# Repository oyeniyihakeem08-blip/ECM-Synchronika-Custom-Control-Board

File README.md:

Project Description

This specification defines a custom control PCB to replace the factory GICAR control board and PID controller in an ECM Synchronika dual-boiler espresso machine. The design must be:

- **Plug & Play**: Direct replacement using existing machine wiring
- **Reversible**: Original equipment can be reinstalled without modification
- **Universal Voltage**: Support 100-240V AC, 50/60Hz worldwide operation
- **Production Ready**: Suitable for small-batch or volume manufacturing

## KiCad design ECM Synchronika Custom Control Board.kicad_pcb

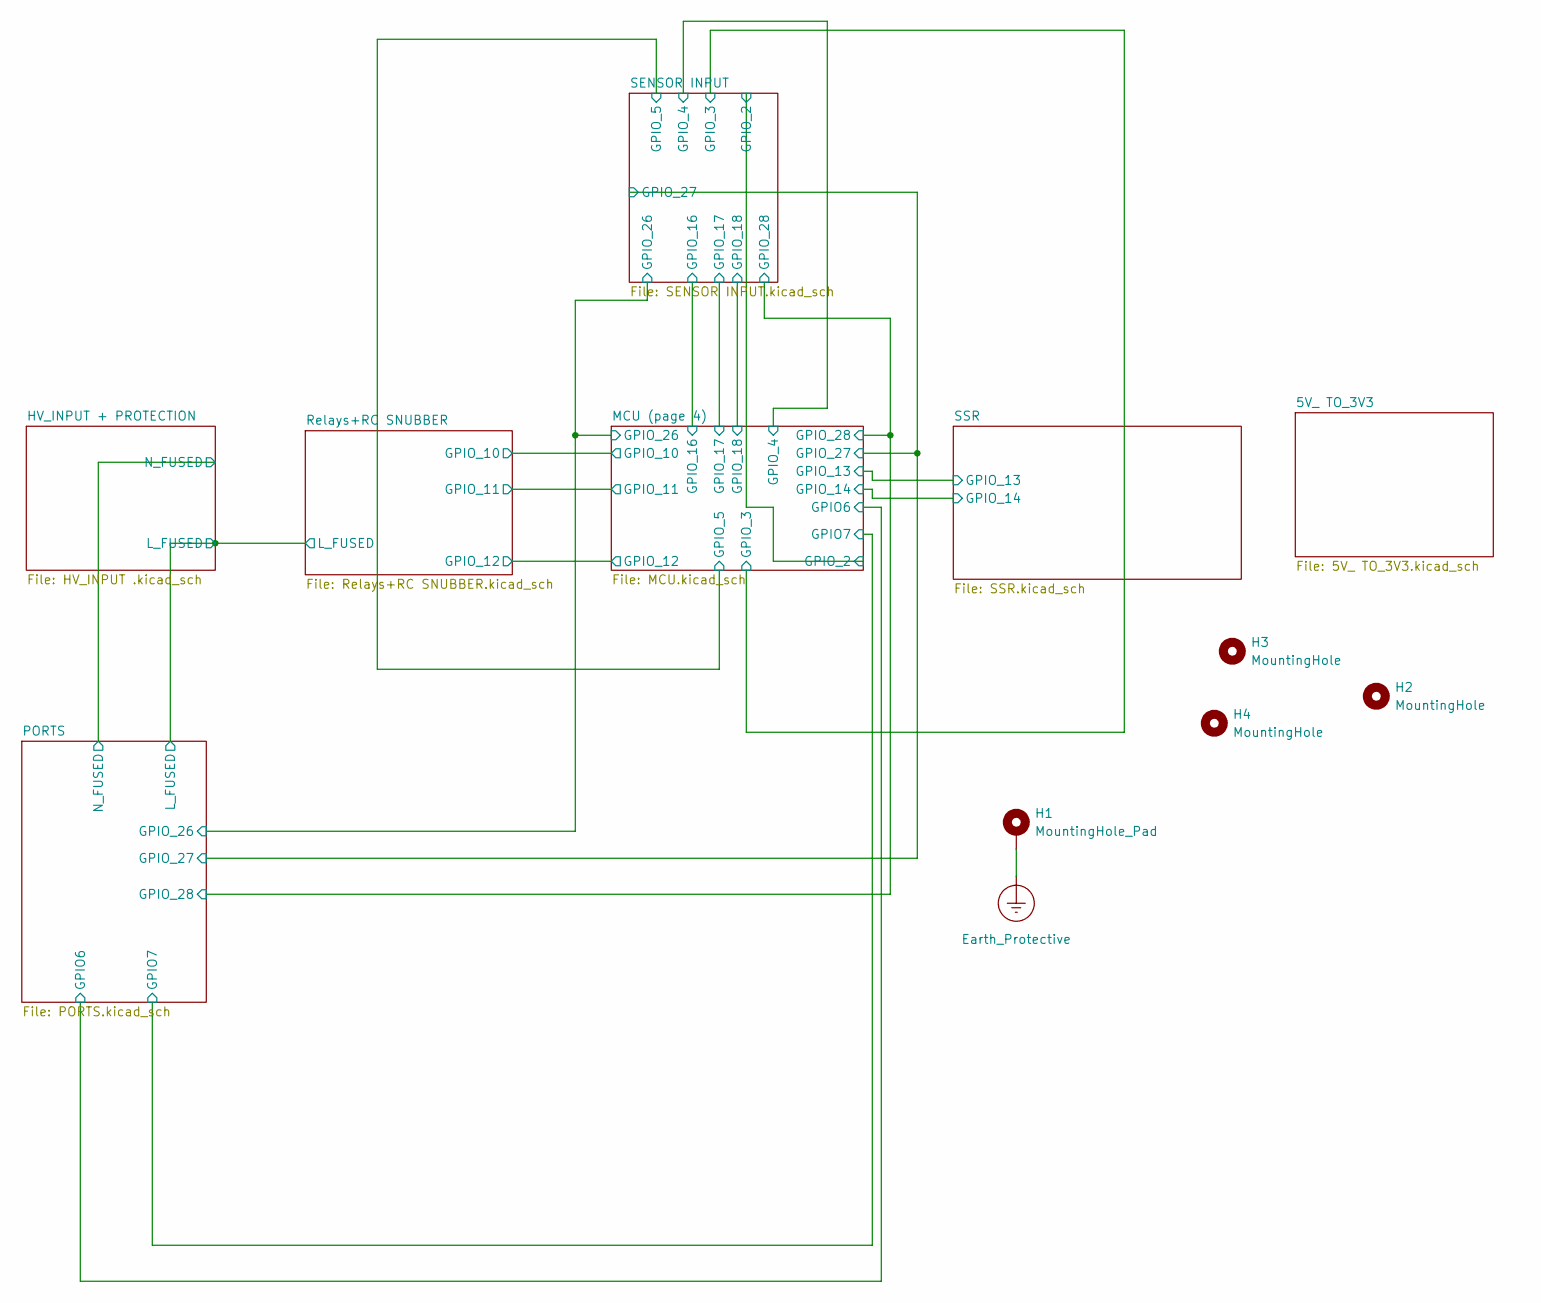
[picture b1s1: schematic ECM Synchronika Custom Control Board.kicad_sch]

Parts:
H1: MountingHole_Pad; MountingHole_3.2mm_M3_ISO7380_Pad_TopBottom
H2, H3, H4: MountingHole; MountingHole_3.2mm_M3_ISO14580

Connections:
Earth_Protective: H1.1; also elsewhere on the board

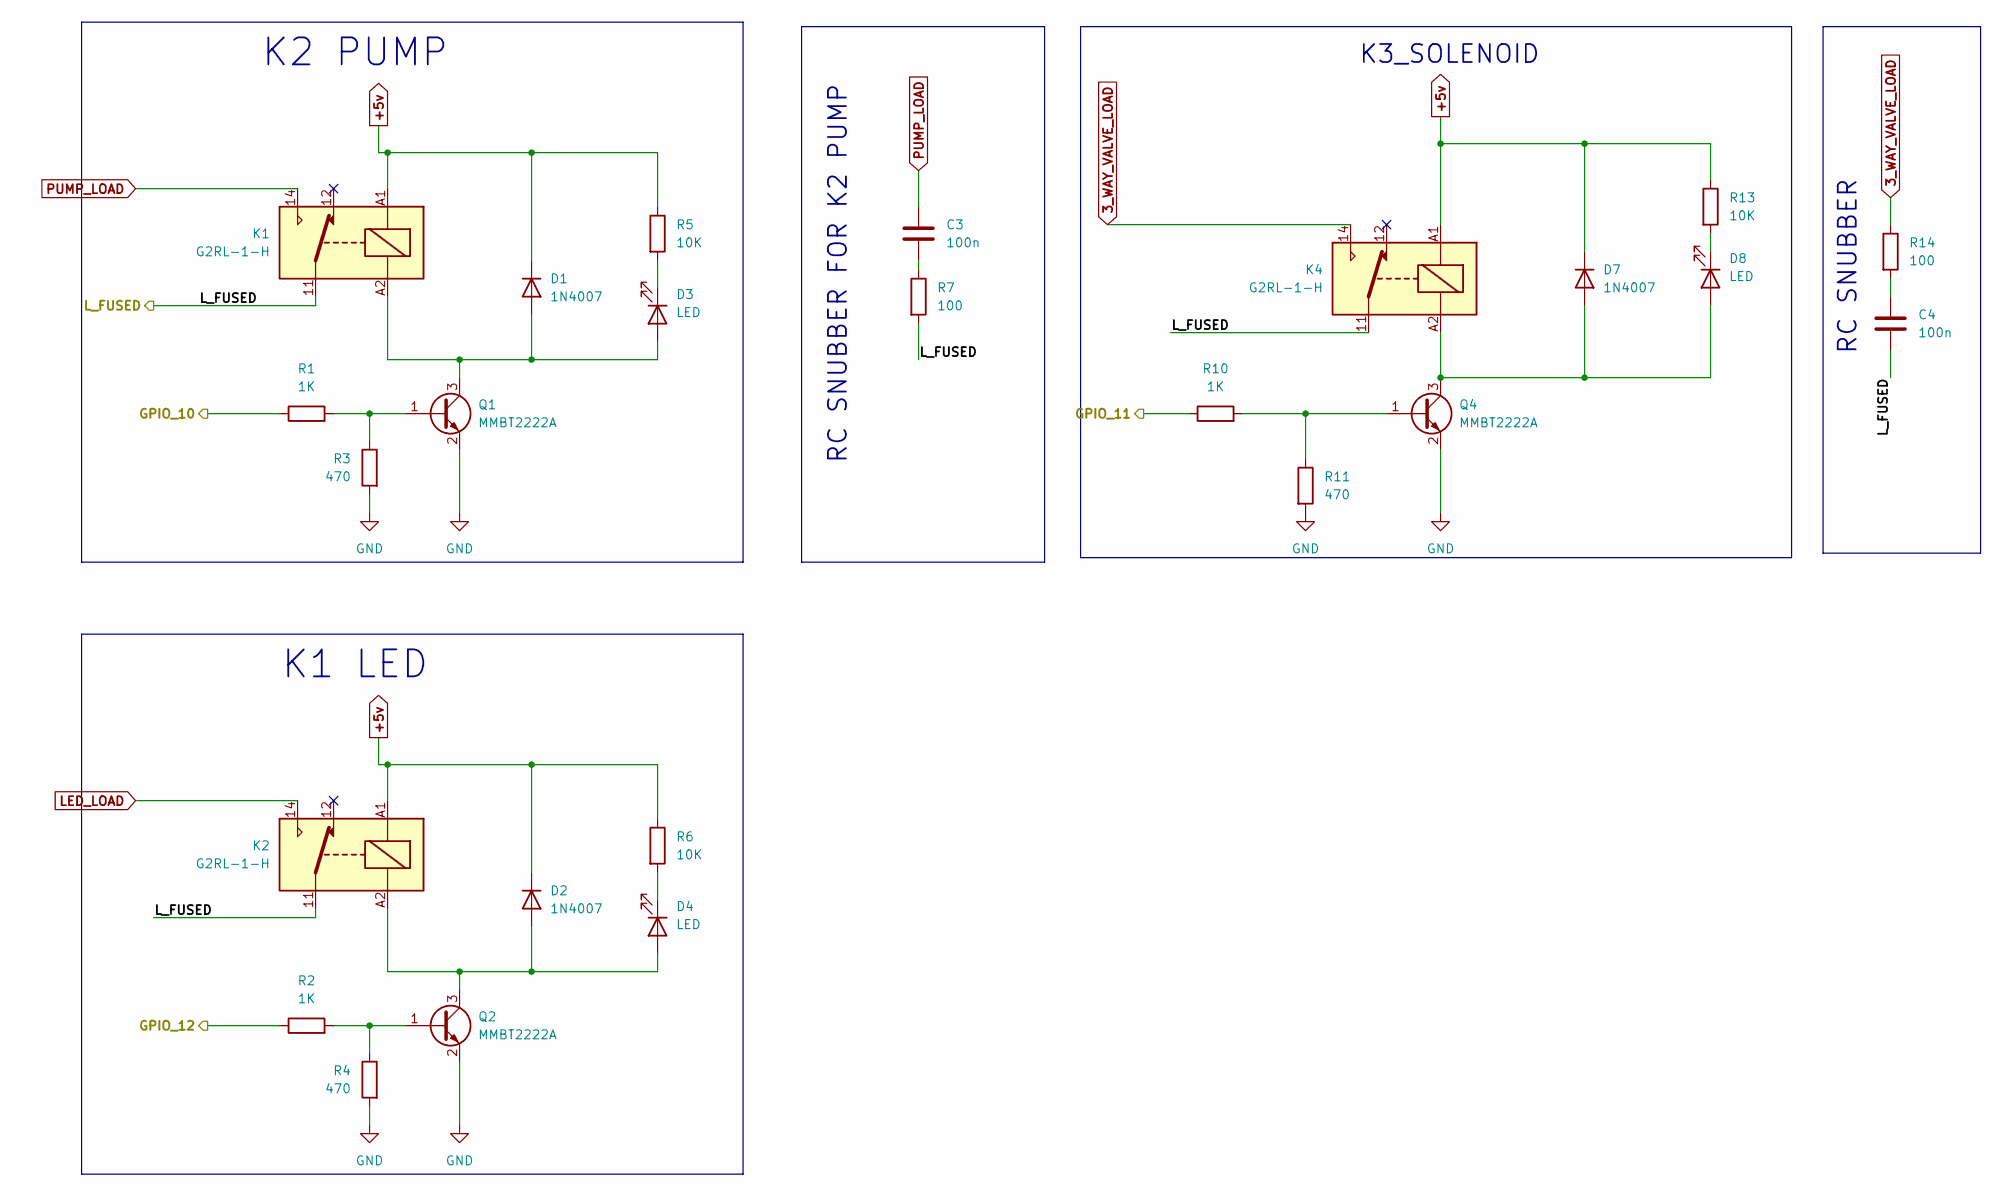
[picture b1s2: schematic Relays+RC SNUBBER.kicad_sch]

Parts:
C3, C4: 100n; C_Rect_L26.5mm_W11.5mm_P22.50mm_MKS4
D1, D2, D7: 1N4007; D_SMA
D3, D4, D8: LED; LED_0805_2012Metric
K1, K2, K4: G2RL-1-H; Relay_SPDT_Omron_G2RL-1 MODIFIED
Q1, Q2, Q4: MMBT2222A; SOT-23
R1, R2, R10: 1K; R_0805_2012Metric
R3, R4, R11: 470; R_0805_2012Metric
R5, R6, R13: 10K; R_0805_2012Metric
R7, R14: 100; R_1210_3225Metric

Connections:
3_WAY_VALVE_LOAD: K4.14, R14.1; also elsewhere on the board
+5v: D1.1 (K), D2.1 (K), D7.1 (K), K1.A1, K2.A1, K4.A1, R5.1, R6.1, R13.1; also elsewhere on the board
/HV_INPUT + PROTECTION/L_FUSED: C4.2, K1.11, K2.11, K4.11, R7.2; also elsewhere on the board
/MCU (page 4)/GPIO_10: R1.1; also elsewhere on the board
/MCU (page 4)/GPIO_11: R10.1; also elsewhere on the board
/MCU (page 4)/GPIO_12: R2.1; also elsewhere on the board
GND: Q1.2 (E), Q2.2 (E), Q4.2 (E), R3.2, R4.2, R11.2; also elsewhere on the board
LED_LOAD: K2.14; also elsewhere on the board
unnamed: C3.2, R7.1
unnamed: C4.1, R14.2
unnamed: D1.2 (A), D3.2 (A), K1.A2, Q1.3 (C)
unnamed: D2.2 (A), D4.2 (A), K2.A2, Q2.3 (C)
unnamed: D3.1 (K), R5.2
unnamed: D4.1 (K), R6.2
unnamed: D7.2 (A), D8.2 (A), K4.A2, Q4.3 (C)
unnamed: D8.1 (K), R13.2
unnamed: Q1.1 (B), R1.2, R3.1
unnamed: Q2.1 (B), R2.2, R4.1
unnamed: Q4.1 (B), R10.2, R11.1
PUMP_LOAD: C3.1, K1.14; also elsewhere on the board

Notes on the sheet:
K1 LED
RC SNUBBER
K2 PUMP
RC SNUBBER FOR K2 PUMP
K3_SOLENOID

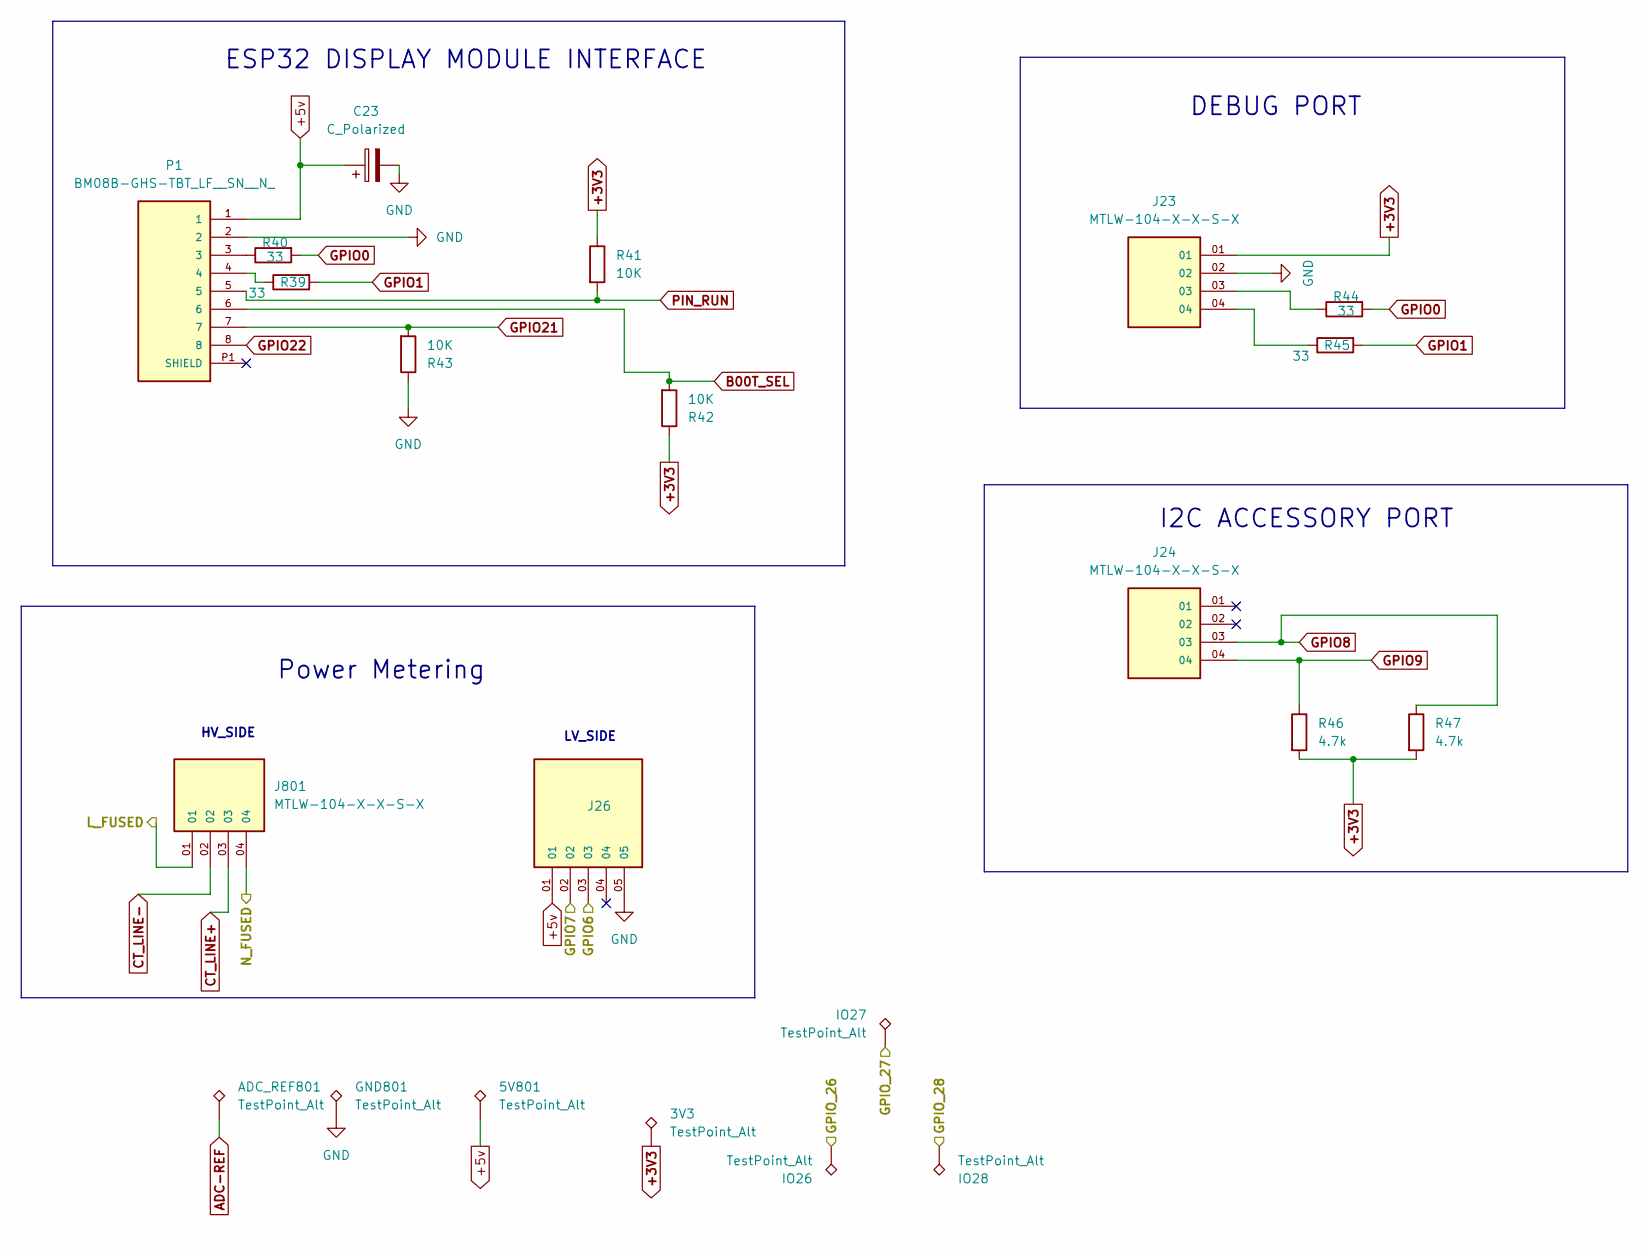
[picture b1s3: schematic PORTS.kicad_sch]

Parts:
3V3, 5V801: TestPoint_Alt; Pin_D1.0mm_L10.0mm_LooseFit
ADC_REF801: TestPoint_Alt; Pin_D1.0mm_L10.0mm_LooseFit
C23: C_Polarized; CP_Elec_5x5.4
GND801: TestPoint_Alt; Pin_D1.0mm_L10.0mm_LooseFit
IO26, IO27, IO28: TestPoint_Alt; Pin_D1.0mm_L10.0mm_LooseFit
J23, J24, J801: MTLW-104-X-X-S-X; SAMTEC_MTLW-104-X-X-S-X; PARTREV A
J26: TSW-105-05-L-S-LL; SAMTEC_TSW-105-05-L-S-LL; PARTREV R
P1: BM08B-GHS-TBT_LF__SN__N_; JST_BM08B-GHS-TBT_LF__SN__N_
R39, R40, R44, R45: 33; R_0805_2012Metric
R41, R42, R43: 10K; R_0603_1608Metric
R46, R47: 4.7k; R_0603_1608Metric

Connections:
+3V3: 3V3.1, J23.01, R41.1, R42.1, R46.2, R47.2; also elsewhere on the board
+5v: 5V801.1, C23.1, J26.01, P1.1; also elsewhere on the board
/HV_INPUT + PROTECTION/L_FUSED: J801.01; also elsewhere on the board
/HV_INPUT + PROTECTION/N_FUSED: J801.04; also elsewhere on the board
/MCU (page 4)/GPIO6: J26.03; also elsewhere on the board
/MCU (page 4)/GPIO7: J26.02; also elsewhere on the board
/MCU (page 4)/GPIO_26: IO26.1; also elsewhere on the board
/MCU (page 4)/GPIO_27: IO27.1; also elsewhere on the board
/SENSOR INPUT/GPIO_28: IO28.1; also elsewhere on the board
ADC-REF: ADC_REF801.1; also elsewhere on the board
B00T_SEL: P1.6, R42.2; also elsewhere on the board
CT_LINE+: J801.03; also elsewhere on the board
CT_LINE-: J801.02; also elsewhere on the board
GND: C23.2, GND801.1, J23.02, J26.05, P1.2, R43.1; also elsewhere on the board
GPIO0: R40.2, R44.2; also elsewhere on the board
GPIO1: R39.2, R45.2; also elsewhere on the board
GPIO8: J24.03, R47.1; also elsewhere on the board
GPIO9: J24.04, R46.1; also elsewhere on the board
GPIO21: P1.7, R43.2; also elsewhere on the board
GPIO22: P1.8; also elsewhere on the board
unnamed: J23.03, R44.1
unnamed: J23.04, R45.1
unnamed: P1.3, R40.1
unnamed: P1.4, R39.1
PIN_RUN: P1.5, R41.2; also elsewhere on the board

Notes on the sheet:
DEBUG PORT
ESP32 DISPLAY MODULE INTERFACE
I2C ACCESSORY PORT
HV_SIDE
LV_SIDE
Power Metering

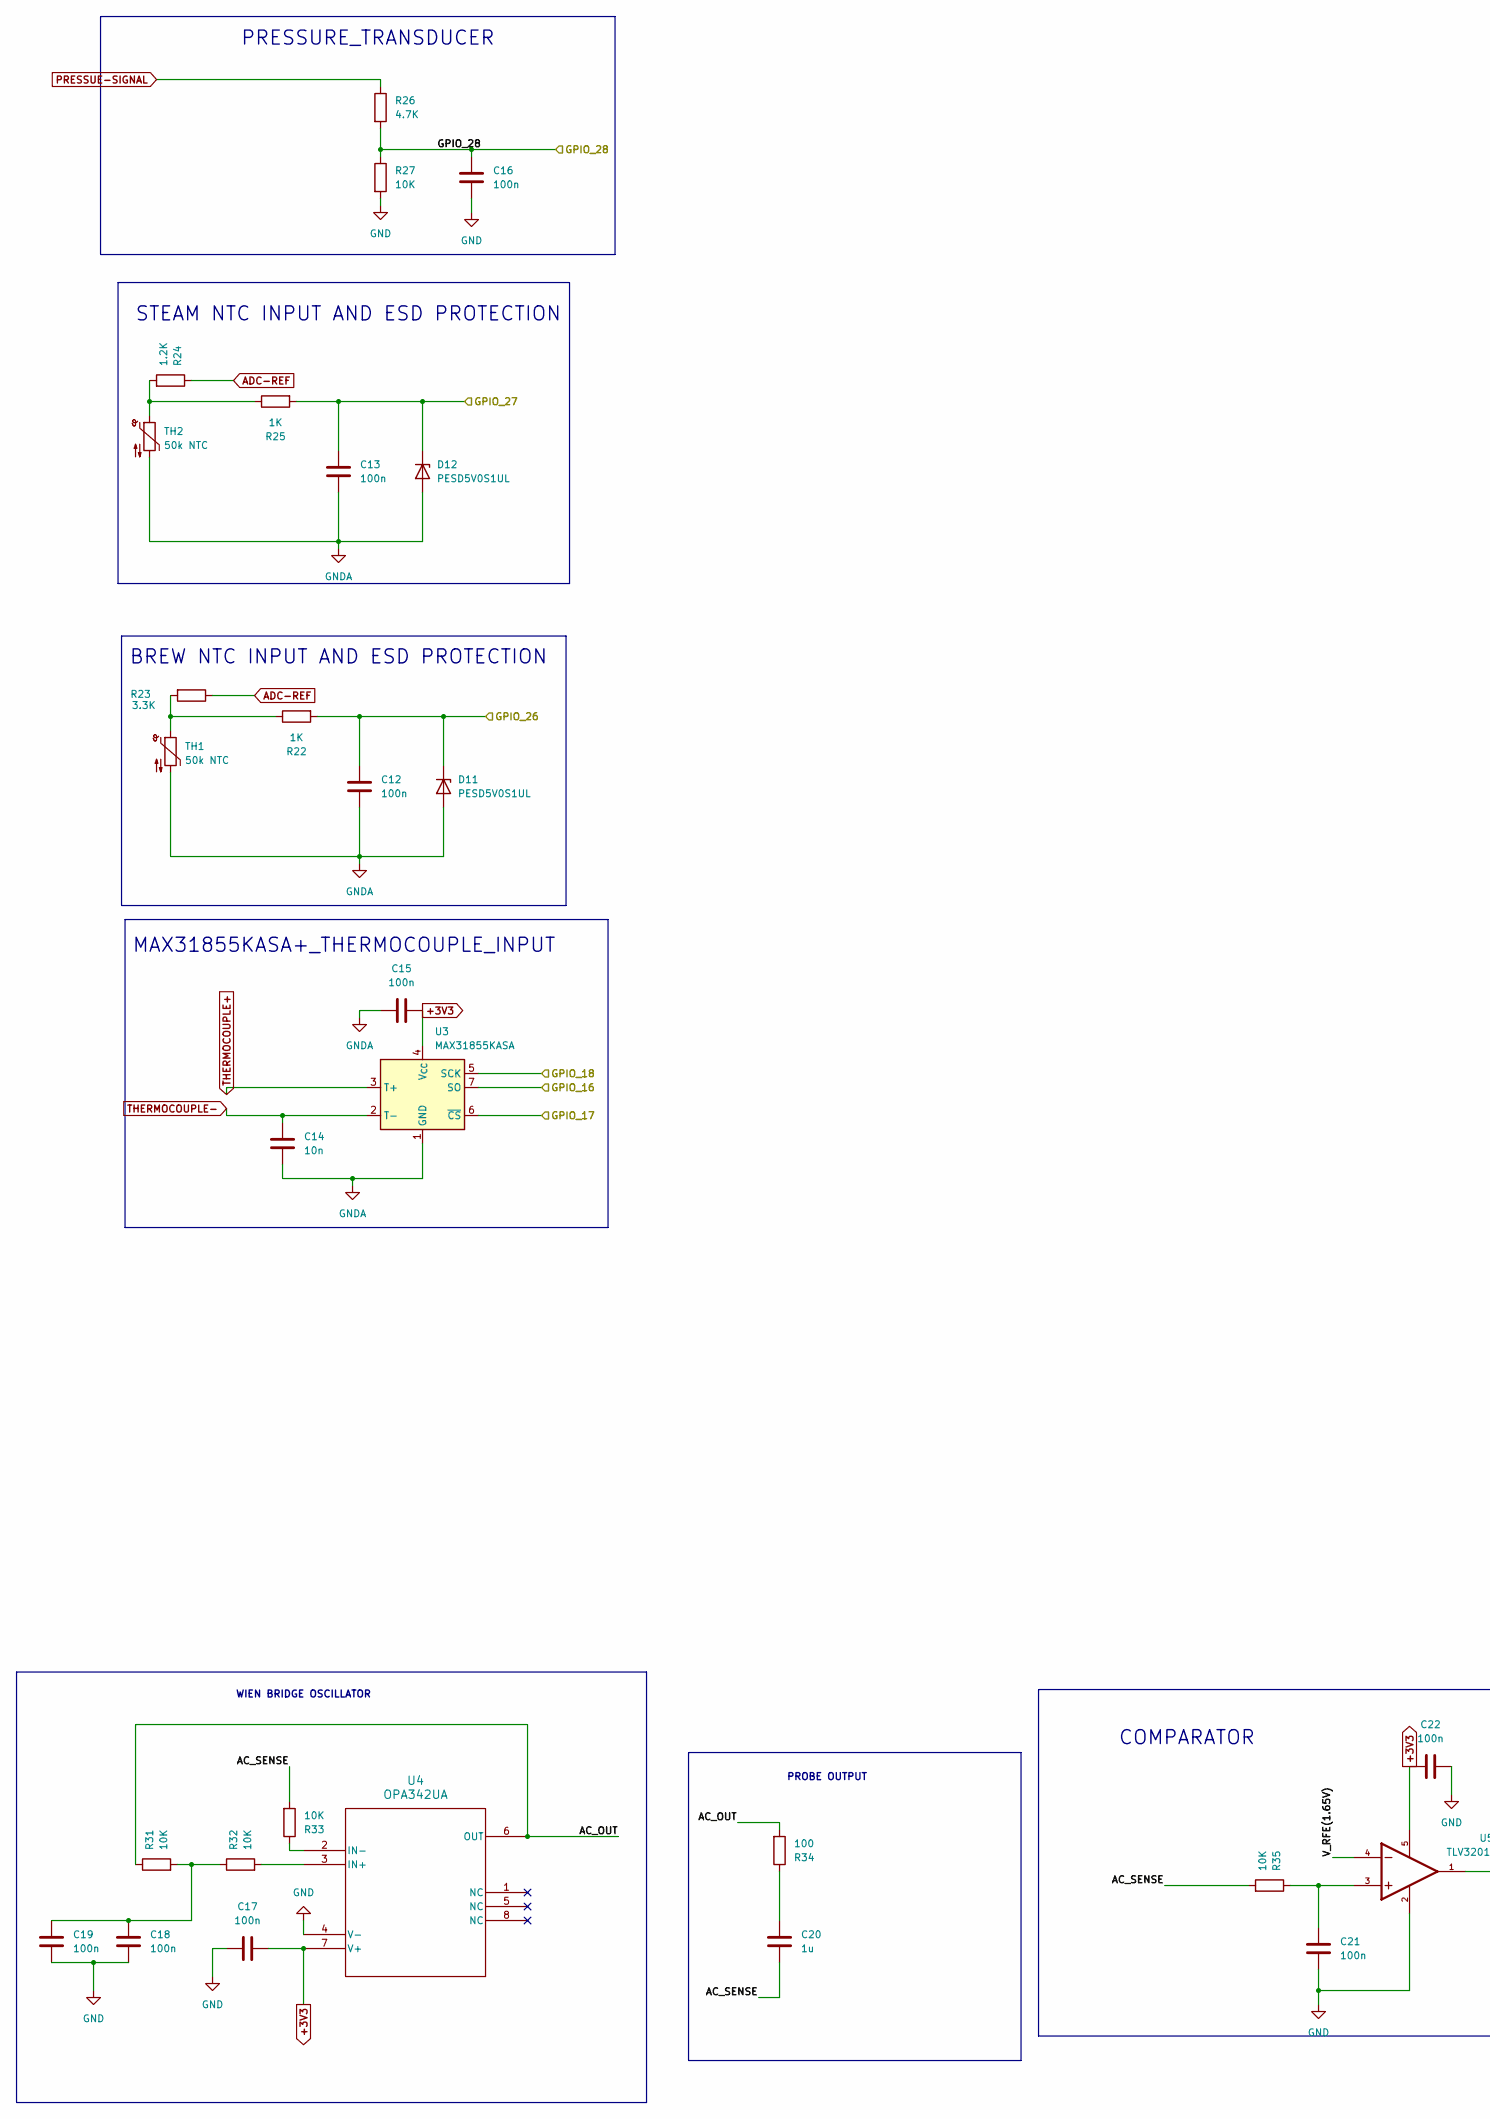
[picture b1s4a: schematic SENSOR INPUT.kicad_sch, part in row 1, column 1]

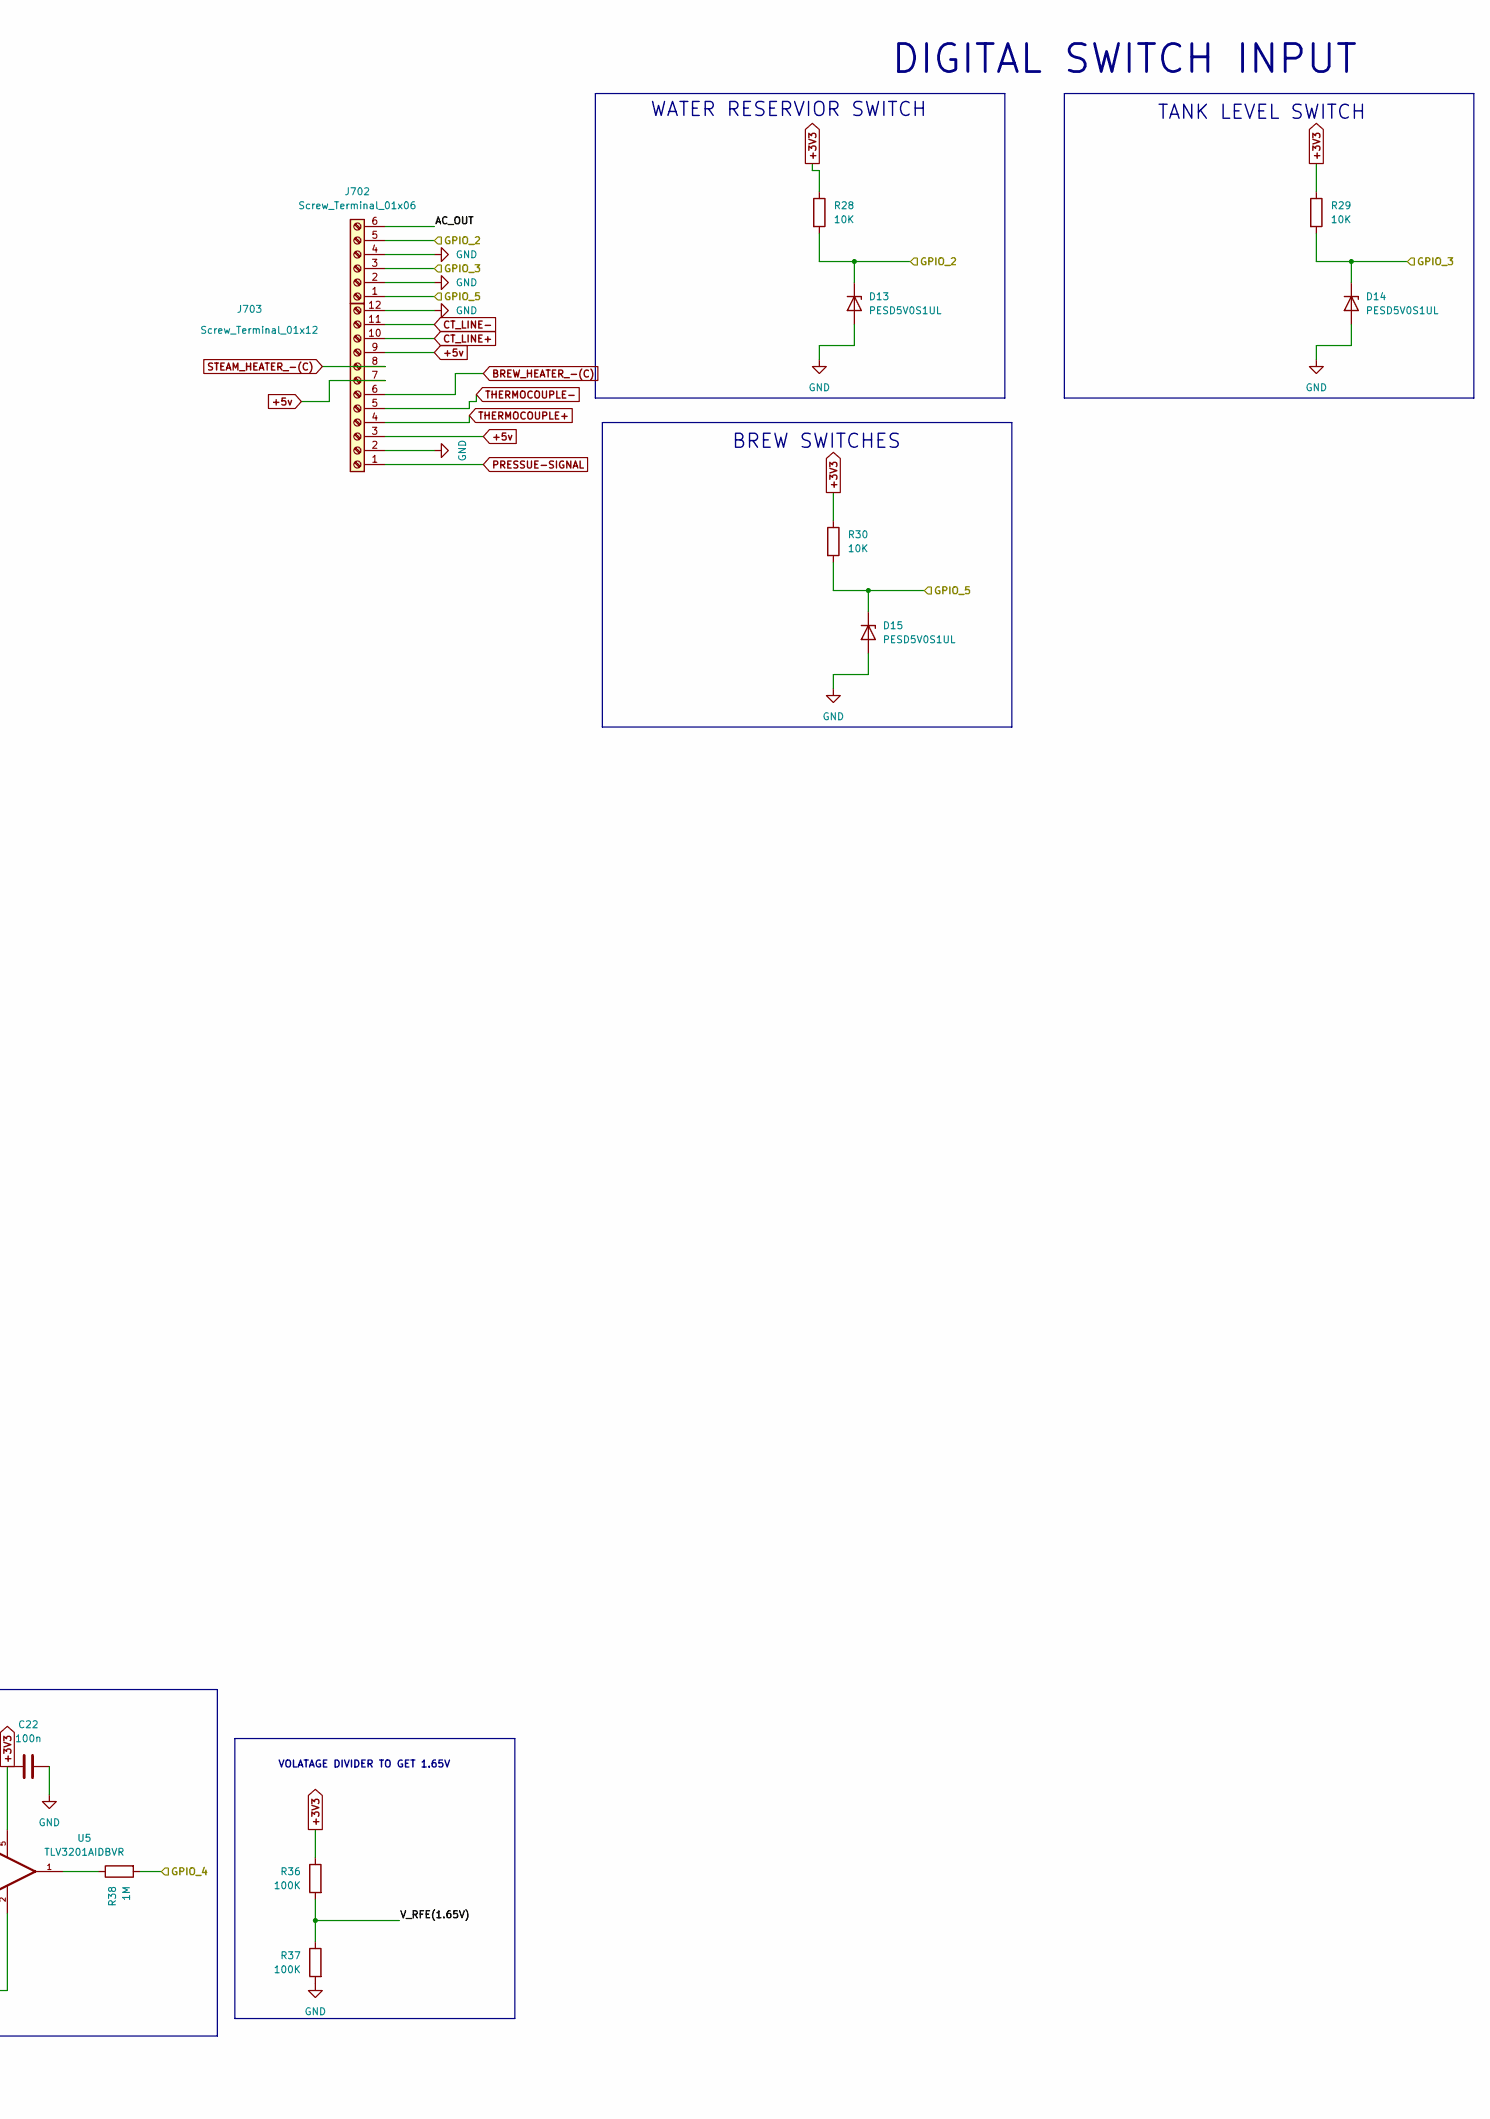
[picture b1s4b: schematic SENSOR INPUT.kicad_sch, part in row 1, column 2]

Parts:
C12, C13, C15, C16: 100n; C_0805_2012Metric
C14: 10n; C_0805_2012Metric
C17, C18, C19, C21, C22: 100n; C_0603_1608Metric
C20: 1u; C_0603_1608Metric
D11, D12, D13, D14, D15: PESD5V0S1UL; D_SOD-882
J702: Screw_Terminal_01x06; TerminalBlock_Phoenix_MPT-0,5-6-2.54_1x06_P2.54mm_Horizontal
J703: Screw_Terminal_01x12; TerminalBlock_Phoenix_MPT-0,5-12-2.54_1x12_P2.54mm_Horizont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
R22, R25: 1K; R_0805_2012Metric
R23: 3.3K; R_0805_2012Metric
R24: 1.2K; R_0805_2012Metric
R26: 4.7K; R_0805_2012Metric
R27, R28, R29, R30, R31, R32, R33, R35: 10K; R_0805_2012Metric
R34: 100; R_0805_2012Metric
R36, R37: 100K; R_0805_2012Metric
R38: 1M; R_0805_2012Metric
TH1, TH2: 50k NTC; R_0603_1608Metric
U3: MAX31855KASA; SOIC-8_3.9x4.9mm_P1.27mm
U4: OPA342UA; D8
U5: TLV3201AIDBVR; COMPARTOR_SOT95P280X145-5N; PARTREV B

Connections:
+3V3: C15.2, C17.2, C22.2, R28.1, R29.1, R30.1, R36.1, U3.4 (V_{CC}), U4.7 (V+), U5.5; also elsewhere on the board
+5v: J703.3, J703.7, J703.9; also elsewhere on the board
/MCU (page 4)/GPIO_2: D13.1 (K), J702.5, R28.2; also elsewhere on the board
/MCU (page 4)/GPIO_3: D14.1 (K), J702.3, R29.2; also elsewhere on the board
/MCU (page 4)/GPIO_4: R38.2; also elsewhere on the board
/MCU (page 4)/GPIO_5: D15.1 (K), J702.1, R30.2; also elsewhere on the board
/MCU (page 4)/GPIO_16: U3.7 (SO); also elsewhere on the board
/MCU (page 4)/GPIO_17: U3.6 (~CS); also elsewhere on the board
/MCU (page 4)/GPIO_18: U3.5 (SCK); also elsewhere on the board
/MCU (page 4)/GPIO_26: C12.1, D11.1 (K), R22.2; also elsewhere on the board
/MCU (page 4)/GPIO_27: C13.1, D12.1 (K), R25.2; also elsewhere on the board
/SENSOR INPUT/AC_OUT: J702.6, R31.1, R34.2, U4.6 (OUT)
/SENSOR INPUT/AC_SENSE: C20.1, R33.2, R35.2
/SENSOR INPUT/GPIO_28: C16.1, R26.2, R27.1; also elsewhere on the board
/SENSOR INPUT/V_RFE(1.65V): R36.2, R37.1, U5.4
ADC-REF: R23.1, R24.1; also elsewhere on the board
BREW_HEATER_-(C): J703.6; also elsewhere on the board
CT_LINE+: J703.10; also elsewhere on the board
CT_LINE-: J703.11; also elsewhere on the board
GND: C16.2, C17.1, C18.1, C19.1, C21.1, C22.1, D13.2 (A), D14.2 (A), D15.2 (A), J702.2, J702.4, J703.2, J703.12, R27.2, R37.2, U4.4 (V-), U5.2; also elsewhere on the board
GNDA: C12.2, C13.2, C14.2, C15.1, D11.2 (A), D12.2 (A), TH1.2, TH2.2, U3.1 (GND); also elsewhere on the board
unnamed: C18.2, C19.2, R31.2, R32.1
unnamed: C20.2, R34.1
unnamed: C21.2, R35.1, U5.3
unnamed: R22.1, R23.2, TH1.1
unnamed: R24.2, R25.1, TH2.1
unnamed: R38.1, U5.1
unnamed: R32.2, U4.3 (IN+)
unnamed: R33.1, U4.2 (IN-)
PRESSUE-SIGNAL: J703.1, R26.1
STEAM_HEATER_-(C): J703.8; also elsewhere on the board
THERMOCOUPLE+: J703.4, U3.3 (T+)
THERMOCOUPLE-: C14.1, J703.5, U3.2 (T-)

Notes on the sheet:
PROBE OUTPUT
DIGITAL SWITCH INPUT
WIEN BRIDGE OSCILLATOR
BREW NTC INPUT AND ESD PROTECTION
WATER RESERVIOR SWITCH
MAX31855KASA+_THERMOCOUPLE_INPUT
VOLATAGE DIVIDER TO GET 1.65V
COMPARATOR
STEAM NTC INPUT AND ESD PROTECTION
TANK LEVEL SWITCH
BREW SWITCHES
PRESSURE_TRANSDUCER

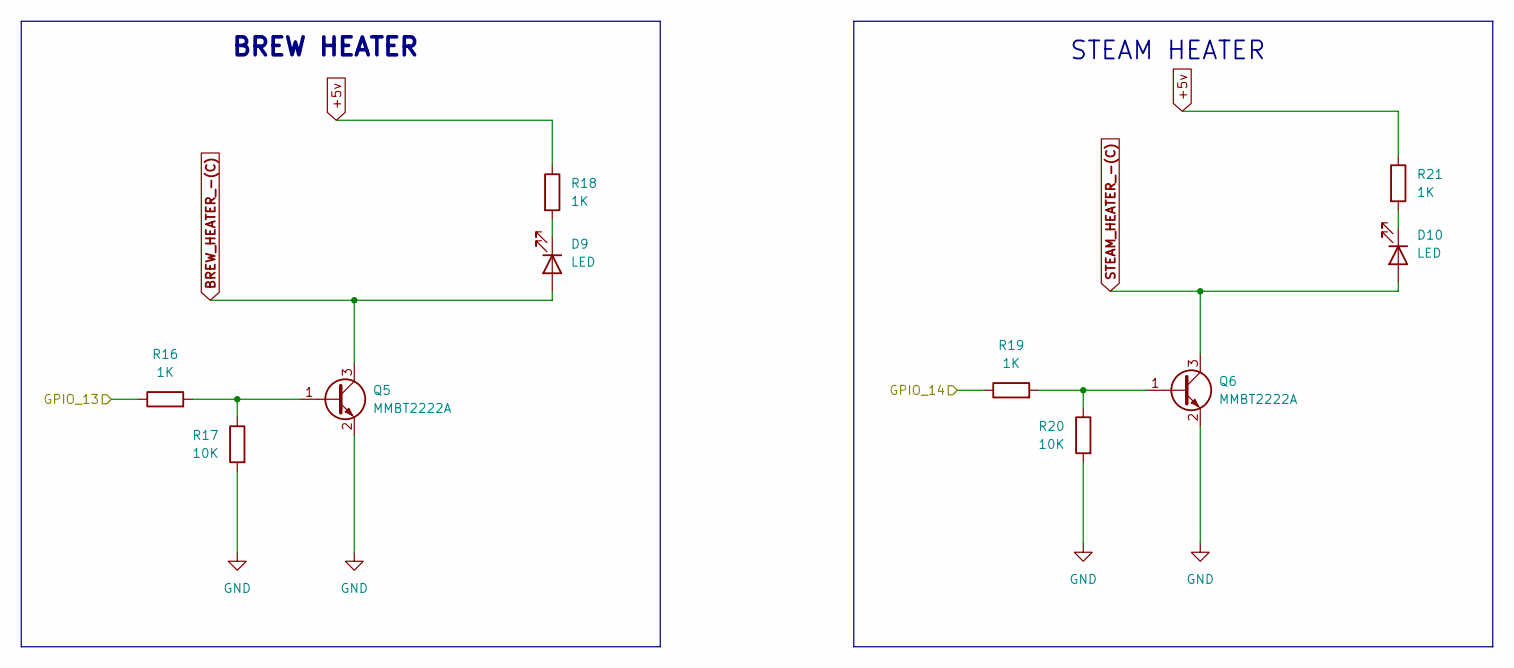
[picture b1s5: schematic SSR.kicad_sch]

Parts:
D9, D10: LED; LED_0805_2012Metric
Q5, Q6: MMBT2222A; SOT-23
R16, R18, R19, R21: 1K; R_0805_2012Metric
R17, R20: 10K; R_0805_2012Metric

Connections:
+5v: R18.1, R21.1; also elsewhere on the board
/MCU (page 4)/GPIO_13: R16.1; also elsewhere on the board
/MCU (page 4)/GPIO_14: R19.1; also elsewhere on the board
BREW_HEATER_-(C): D9.2 (A), Q5.3 (C); also elsewhere on the board
GND: Q5.2 (E), Q6.2 (E), R17.2, R20.2; also elsewhere on the board
unnamed: D9.1 (K), R18.2
unnamed: D10.1 (K), R21.2
unnamed: Q5.1 (B), R16.2, R17.1
unnamed: Q6.1 (B), R19.2, R20.1
STEAM_HEATER_-(C): D10.2 (A), Q6.3 (C); also elsewhere on the board

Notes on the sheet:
STEAM HEATER
BREW HEATER

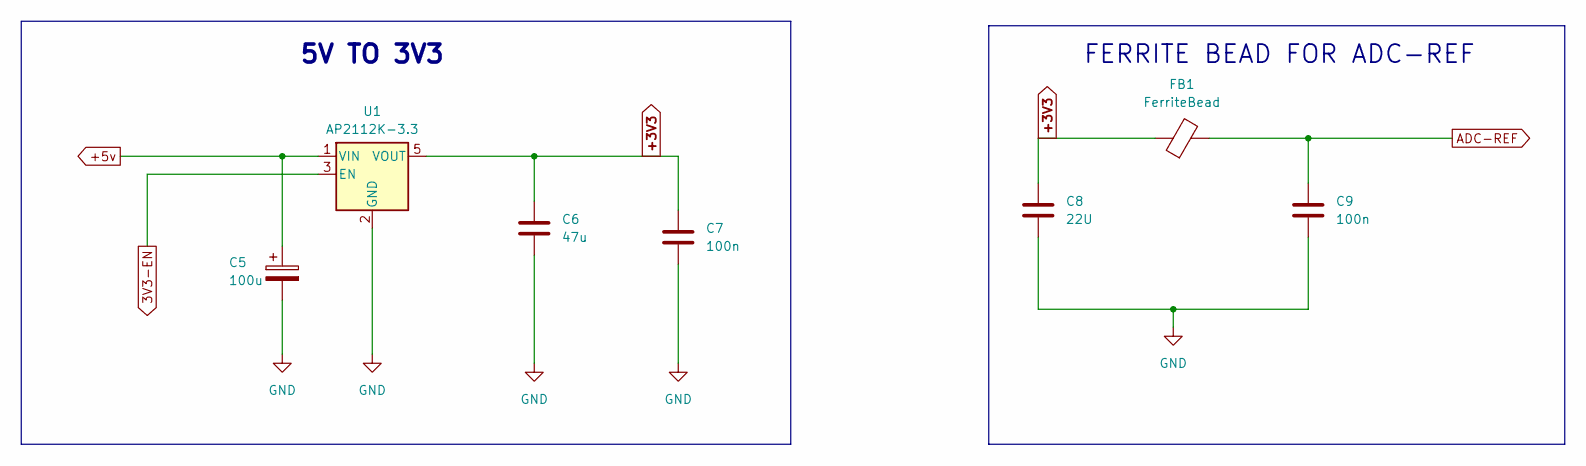
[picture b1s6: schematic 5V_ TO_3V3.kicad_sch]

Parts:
C5: 100u; CP_Elec_6.3x5.9
C6: 47u; C_1206_3216Metric; voltage 10v
C7, C9: 100n; C_0805_2012Metric
C8: 22U; C_1206_3216Metric
FB1: FerriteBead; L_0603_1608Metric
U1: AP2112K-3.3; SOT-23-5

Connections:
3V3-EN: U1.3 (EN); also elsewhere on the board
+3V3: C6.1, C7.1, C8.1, FB1.1, U1.5 (VOUT); also elsewhere on the board
+5v: C5.1, U1.1 (VIN); also elsewhere on the board
ADC-REF: C9.1, FB1.2; also elsewhere on the board
GND: C5.2, C6.2, C7.2, C8.2, C9.2, U1.2 (GND); also elsewhere on the board

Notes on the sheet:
FERRITE BEAD FOR ADC-REF
5V TO 3V3

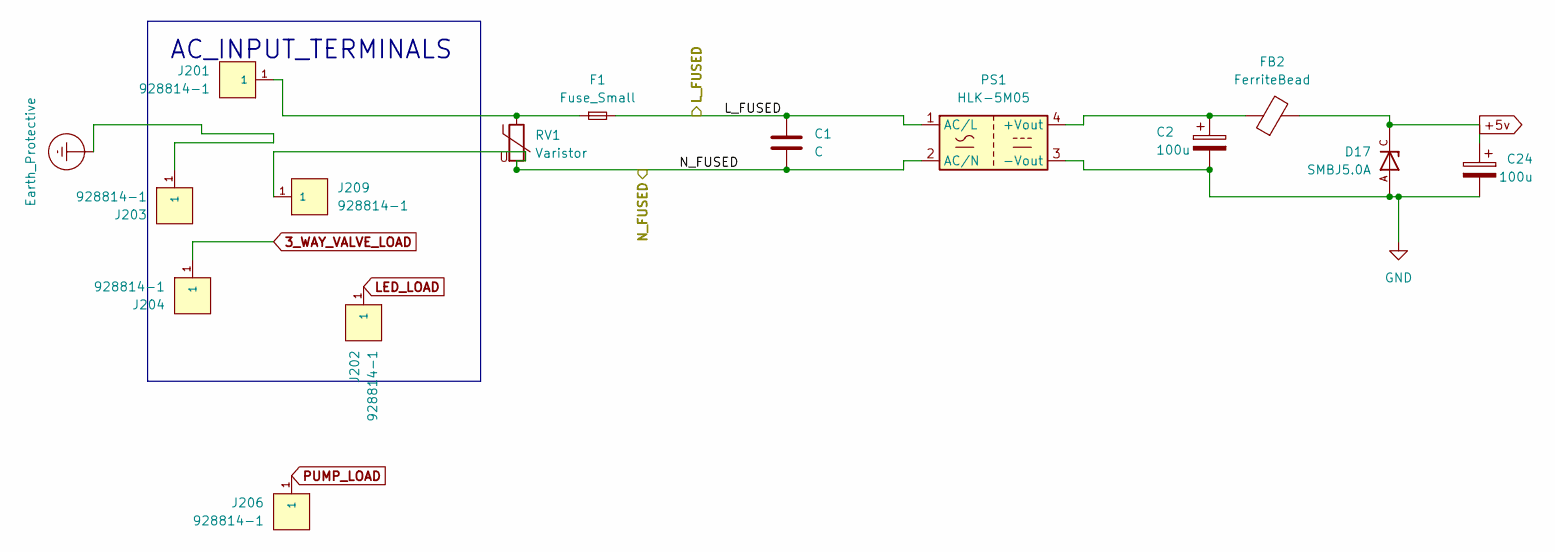
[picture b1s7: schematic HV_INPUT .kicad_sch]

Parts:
C1: C; C_Rect_L18.0mm_W5.0mm_P15.00mm_FKS3_FKP3
C2, C24: 100u; CP_Elec_6.3x5.9
D17: SMBJ5.0A; DIOM4336X265N; PARTREV F2102
F1: Fuse_Small; Fuseholder_Clip-5x20mm_Littelfuse_111_Inline_P20.00x5.00mm_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
FB2: FerriteBead; L_0603_1608Metric
J201, J202, J203, J204, J206, J209: 928814-1; TE_928814-1; PARTREV 3-11
PS1: HLK-5M05; Converter_ACDC_Hi-Link_HLK-5Mxx
RV1: Varistor; RV_Disc_D15.5mm_W4.9mm_P7.5mm

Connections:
3_WAY_VALVE_LOAD: J204.1; also elsewhere on the board
+5v: C24.1, D17.C, FB2.2; also elsewhere on the board
/HV_INPUT + PROTECTION/L_FUSED: C1.1, F1.2, PS1.1 (AC/L); also elsewhere on the board
/HV_INPUT + PROTECTION/N_FUSED: C1.2, J209.1, PS1.2 (AC/N), RV1.2; also elsewhere on the board
Earth_Protective: J203.1; also elsewhere on the board
GND: C2.2, C24.2, D17.A, PS1.3 (-Vout); also elsewhere on the board
LED_LOAD: J202.1; also elsewhere on the board
unnamed: F1.1, J201.1, RV1.1
unnamed: C2.1, FB2.1, PS1.4 (+Vout)
PUMP_LOAD: J206.1; also elsewhere on the board

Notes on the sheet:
AC_INPUT_TERMINALS
